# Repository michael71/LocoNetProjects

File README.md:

# LocoNetProjects

Model Railroad Arduino Projects based on LocoNet and MRRWA code (see https://github.com/mrrwa )

Hardware is "OpenHardware" and in some cases is ported from https://opensx.net projects.

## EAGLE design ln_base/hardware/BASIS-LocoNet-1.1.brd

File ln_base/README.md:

# LocoNetProjects - LN-Base-1.0

Based on the design of the opensx-project "Basisplatine" (see https://opensx.net/projekte/basisplatine/rj45/ ), a new board was designed with an LN interface but the same pin layout for add-on boards - to be able to re-use some of the opensx designs

BETA-currently.

(c) Michael Blank 2017

Model Railroad Arduino Projects based on LocoNet and MRRWA code (see https://github.com/mrrwa )

Hardware is "OpenHardware" and in some cases is ported from https://opensx.net projects.

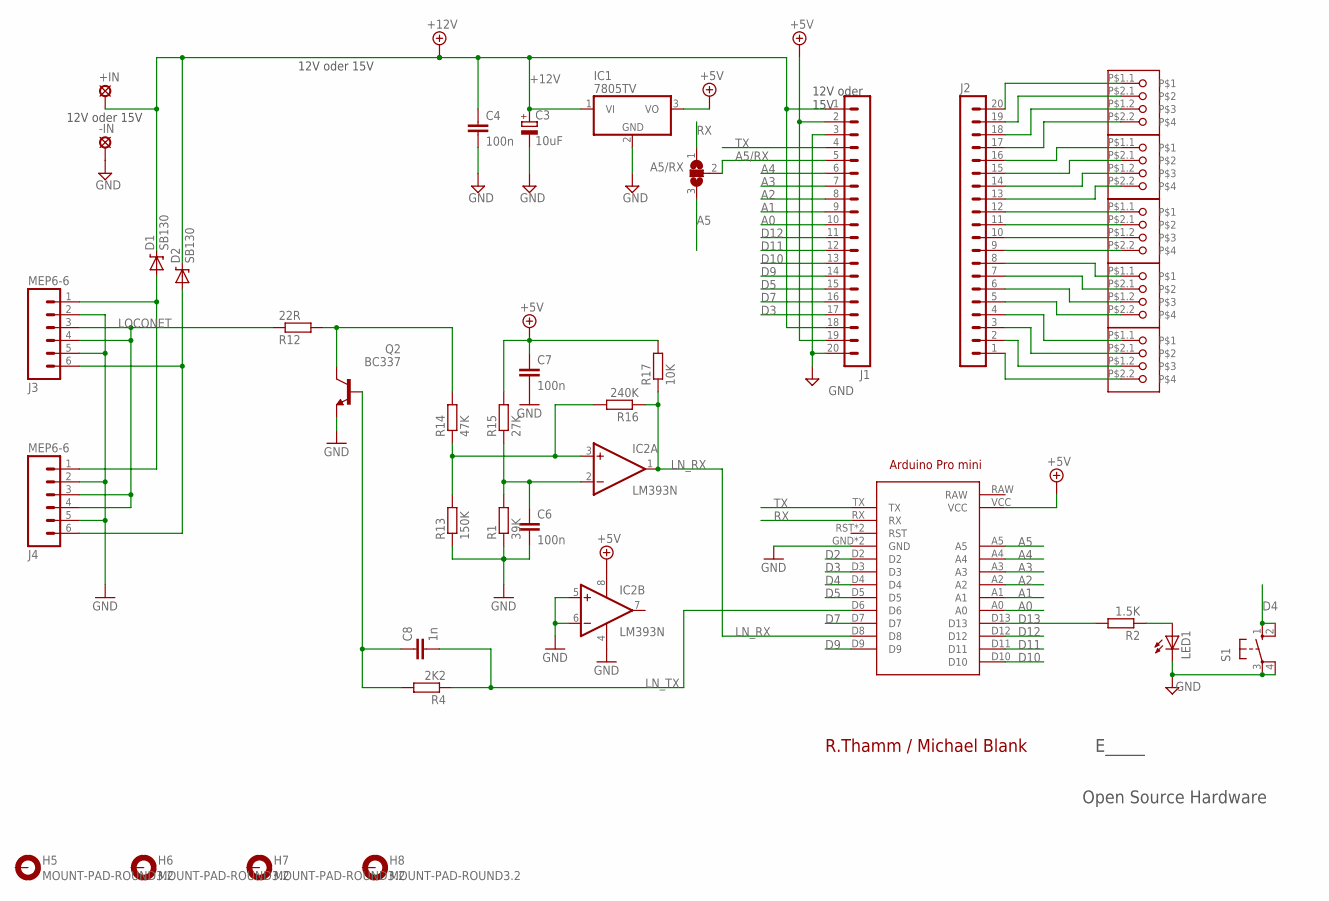
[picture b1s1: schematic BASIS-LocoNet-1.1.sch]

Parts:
+IN: LSP13
-IN: LSP13
A5/RX: SJ2W; SJ_2
ARDUINO2: ArduinoProMini_5V; ARDUINO_PRO_MINI
C3: 10uF; E2,5-7
C4: 100n; C050-025X075
C6, C7: 100n; C025-025X050
C8: 1n; C025-025X050
D1, D2: SB130; DIODE-ZENER
H5, H6, H7, H8: MOUNT-PAD-ROUND3.2; 3,2-PAD
IC1: 7805TV; TO220V
IC2: LM393N; DIL08
J1, J2: MA20-1
J3, J4: MEP6-6; RJ11-6
LED1: LED3MM
Q2: BC337; TO92
R1: 39K; 0207/10
R2: 1.5K; 0207/10
R4: 2K2; 0207/10
R12: 22R; 0207/10
R13: 150K; 0207/10
R14: 47K; 0207/10
R15: 27K; 0207/10
R16: 240K; 0207/10
R17: 10K; 0207/10
S1: 10-XX; B3F-10XX
U$1, U$2, U$3, U$4, U$5: AKL093-06

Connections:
+5V: ARDUINO2.VCC, C7.1, IC1.3 (VO), IC2.8 (V+), J1.2, J1.19, R15.2, R17.2
+12V: +IN.MP, C3.+, C4.1, D1.P$1 (C), D2.P$1 (C), IC1.1 (VI), J1.1, J1.18
A0: ARDUINO2.A0, J1.10
A1: ARDUINO2.A1, J1.9
A2: ARDUINO2.A2, J1.8
A3: ARDUINO2.A3, J1.7
A4: ARDUINO2.A4, J1.6
A5: A5/RX.3, ARDUINO2.A5
A5/RX: A5/RX.2, J1.5
D2: ARDUINO2.D2
D3: ARDUINO2.D3, J1.17
D4: ARDUINO2.D4, S1.1 (S), S1.2 (S1)
D5: ARDUINO2.D5, J1.15
D7: ARDUINO2.D7, J1.16
D9: ARDUINO2.D9, J1.14
D10: ARDUINO2.D10, J1.13
D11: ARDUINO2.D11, J1.12
D12: ARDUINO2.D12, J1.11
D13: ARDUINO2.D13, R2.2
GND: -IN.MP, ARDUINO2.GND, ARDUINO2.GND@1 (GND), C3.-, C4.2, C6.2, C7.2, IC1.2 (GND), IC2.4 (V-), IC2.5 (+IN), IC2.6 (-IN), J1.3, J1.20, J3.2, J3.5, J4.2, J4.5, LED1.K (C), Q2.1 (E), R1.1, R13.1, S1.3, S1.4 (P1)
LN_RX: ARDUINO2.D8, IC2.1 (OUT), R16.1, R17.1
LN_TX: ARDUINO2.D6, C8.2, R4.1
LOCONET: J3.3, J3.4, J4.3, J4.4, R12.1
unnamed: LED1.A, R2.1
unnamed: J2.1, U$4.P$2.2
unnamed: J2.2, U$4.P$1.2
unnamed: J2.3, U$4.P$2.1
unnamed: J2.4, U$4.P$1.1
unnamed: J2.5, U$3.P$2.2
unnamed: J2.6, U$3.P$1.2
unnamed: J2.7, U$3.P$2.1
unnamed: J2.8, U$3.P$1.1
unnamed: J2.9, U$1.P$2.2
unnamed: J2.10, U$1.P$1.2
unnamed: J2.11, U$1.P$2.1
unnamed: J2.12, U$1.P$1.1
unnamed: J2.13, U$2.P$2.2
unnamed: J2.14, U$2.P$1.2
unnamed: J2.15, U$2.P$2.1
unnamed: J2.16, U$2.P$1.1
unnamed: J2.17, U$5.P$2.2
unnamed: J2.18, U$5.P$1.2
unnamed: J2.19, U$5.P$2.1
unnamed: J2.20, U$5.P$1.1
unnamed: D1.P$2 (A), J3.1, J4.1
unnamed: C6.1, IC2.2 (-IN), R1.2, R15.1
unnamed: C8.1, Q2.2 (B), R4.2
unnamed: IC2.3 (+IN), R13.2, R14.1, R16.2
unnamed: Q2.3 (C), R12.2, R14.2
unnamed: D2.P$2 (A), J3.6, J4.6
RX: A5/RX.1, ARDUINO2.RX
TX: ARDUINO2.TX, J1.4

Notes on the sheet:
R.Thamm / Michael Blank
Open Source Hardware
E_____
12V oder 15V
12V oder 15V

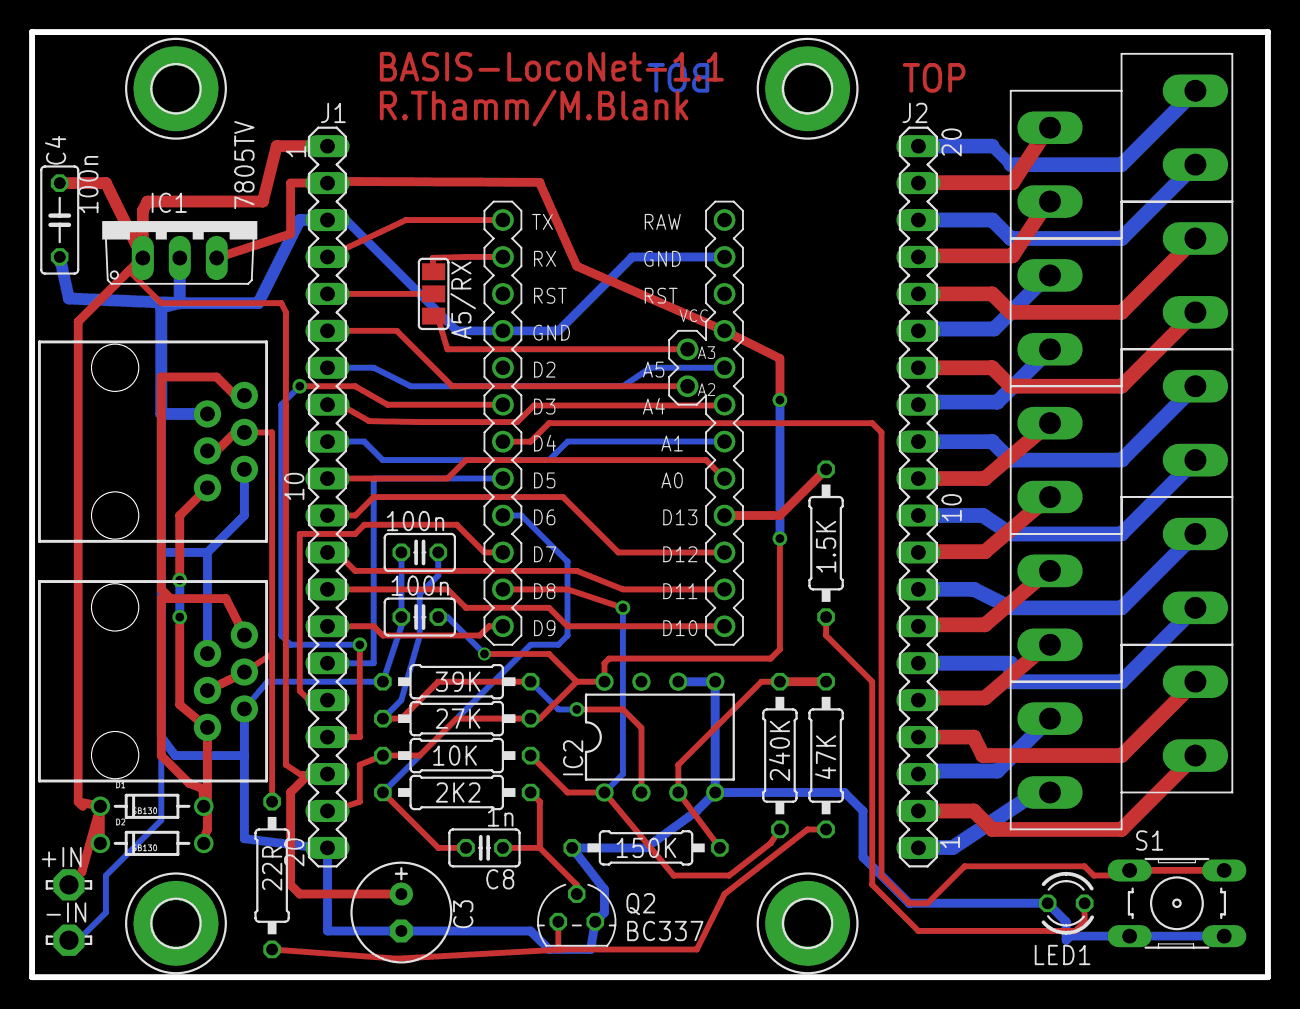
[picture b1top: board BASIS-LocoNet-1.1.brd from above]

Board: 2 copper layers, 85.0 x 65.0 mm, 38 parts (0 on the bottom side), 51 nets.

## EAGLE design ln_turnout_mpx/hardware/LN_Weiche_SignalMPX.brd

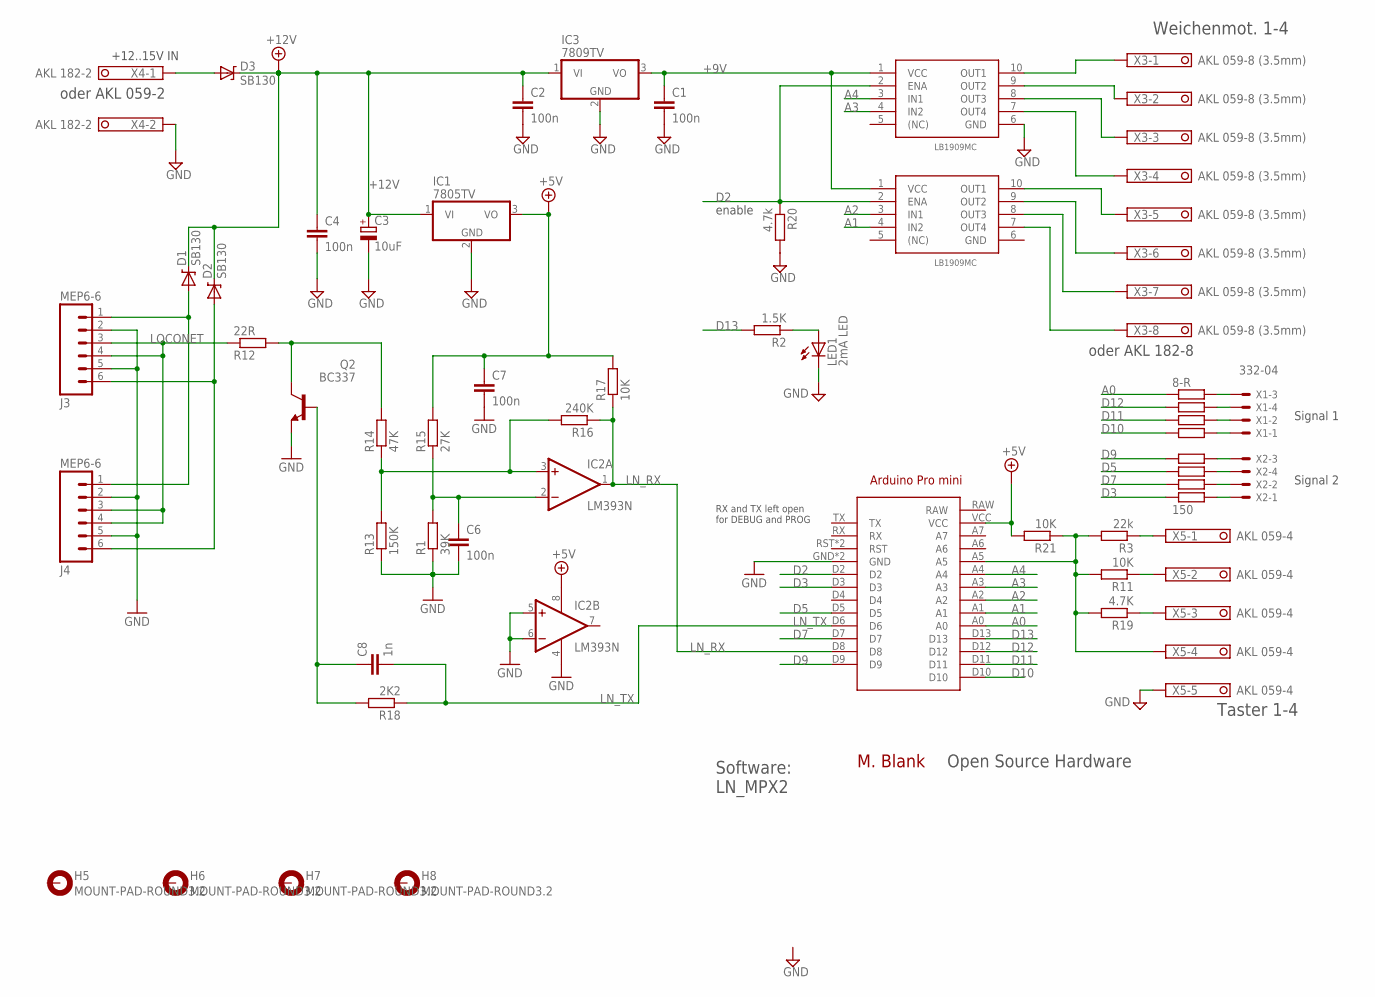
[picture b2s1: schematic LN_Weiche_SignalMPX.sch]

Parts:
8-R: 150; 0207/10
ARDUINO1: ARDUINO_PRO_MINI
C1, C2, C4, C6, C7: 100n; C050-025X075
C3: 10uF; E2,5-7
C8: 1n; C025-025X050
D1, D2, D3: SB130; DIODE-ZENER
H5, H6, H7, H8: MOUNT-PAD-ROUND3.2; 3,2-PAD
IC1: 7805TV; TO220V
IC2: LM393N; DIL08
IC3: 7809TV; TO220V
J3, J4: MEP6-6; RJ11-6
LB1909MC-1, LB1909MC-2: LB1909MC; MSOIC10-1MM
LED1: 2mA LED; LED3MM
Q2: BC337; TO92
R1: 39K; 0207/10
R2: 1.5K; 0207/10
R3: 22k; 0207/10
R4, R5, R6, R7, R8, R9, R10: 150; 0207/10
R11, R17, R21: 10K; 0207/10
R12: 22R; 0207/10
R13: 150K; 0207/10
R14: 47K; 0207/10
R15: 27K; 0207/10
R16: 240K; 0207/10
R18: 2K2; 0207/10
R19: 4.7K; 0207/10
R20: 4.7k; 0207/10
X1, X2: 332-04
X3: AKL 059-8 (3.5mm); 1751303
X4: AKL 182-2; 1751248
X5: AKL 059-4; 1751277

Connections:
+5V: ARDUINO1.VCC, C7.1, IC1.3 (VO), IC2.8 (V+), R15.2, R17.2, R21.2
+9V: C1.1, IC3.3 (VO), LB1909MC-1.1 (VCC), LB1909MC-2.1 (VCC)
+12V: C2.1, C3.+, C4.1, D1.P$1 (C), D2.P$1 (C), D3.P$1 (C), IC1.1 (VI), IC3.1 (VI)
A0: 8-R.1, ARDUINO1.A0
A1: ARDUINO1.A1, LB1909MC-2.4 (IN2)
A2: ARDUINO1.A2, LB1909MC-2.3 (IN1)
A3: ARDUINO1.A3, LB1909MC-1.4 (IN2)
A4: ARDUINO1.A4, LB1909MC-1.3 (IN1)
D2: ARDUINO1.D2, LB1909MC-1.2 (ENA), LB1909MC-2.2 (ENA), R20.1
D3: ARDUINO1.D3, R10.1
D5: ARDUINO1.D5, R8.1
D7: ARDUINO1.D7, R9.1
D9: ARDUINO1.D9, R7.1
D10: ARDUINO1.D10, R6.1
D11: ARDUINO1.D11, R5.1
D12: ARDUINO1.D12, R4.1
D13: ARDUINO1.D13, R2.2
GND: ARDUINO1.GND, ARDUINO1.GND@1 (GND), C1.2, C2.2, C3.-, C4.2, C6.2, C7.2, IC1.2 (GND), IC2.4 (V-), IC2.5 (+IN), IC2.6 (-IN), IC3.2 (GND), J3.2, J3.5, J4.2, J4.5, LB1909MC-1.6 (GND), LB1909MC-2.6 (GND), LED1.K (C), Q2.1 (E), R1.1, R13.1, R20.2, X4.2, X5.5
LN_RX: ARDUINO1.D8, IC2.1 (OUT), R16.1, R17.1
LN_TX: ARDUINO1.D6, C8.2, R18.1
LOCONET: J3.3, J3.4, J4.3, J4.4, R12.1
unnamed: LED1.A, R2.1
unnamed: LB1909MC-1.10 (OUT1), X3.1
unnamed: LB1909MC-1.9 (OUT2), X3.2
unnamed: LB1909MC-1.8 (OUT3), X3.3
unnamed: LB1909MC-1.7 (OUT4), X3.4
unnamed: 8-R.2, X1.3
unnamed: R4.2, X1.4
unnamed: R5.2, X1.2
unnamed: R6.2, X1.1
unnamed: D3.P$2 (A), X4.1
unnamed: R7.2, X2.3
unnamed: R8.2, X2.4
unnamed: R9.2, X2.2
unnamed: R10.2, X2.1
unnamed: LB1909MC-2.10 (OUT1), X3.5
unnamed: LB1909MC-2.9 (OUT2), X3.6
unnamed: LB1909MC-2.8 (OUT3), X3.7
unnamed: LB1909MC-2.7 (OUT4), X3.8
unnamed: ARDUINO1.A5, R3.2, R11.2, R19.2, R21.1, X5.4
unnamed: R3.1, X5.1
unnamed: R11.1, X5.2
unnamed: R19.1, X5.3
unnamed: D1.P$2 (A), J3.1, J4.1
unnamed: C6.1, IC2.2 (-IN), R1.2, R15.1
unnamed: C8.1, Q2.2 (B), R18.2
unnamed: IC2.3 (+IN), R13.2, R14.1, R16.2
unnamed: Q2.3 (C), R12.2, R14.2
unnamed: D2.P$2 (A), J3.6, J4.6

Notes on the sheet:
M. Blank
Open Source Hardware
Signal 1
+12..15V IN
Signal 2
Weichenmot. 1-4
Taster 1-4
oder AKL 059-2
oder AKL 182-8
RX and TX left open for DEBUG and PROG
enable
Software: LN_MPX2

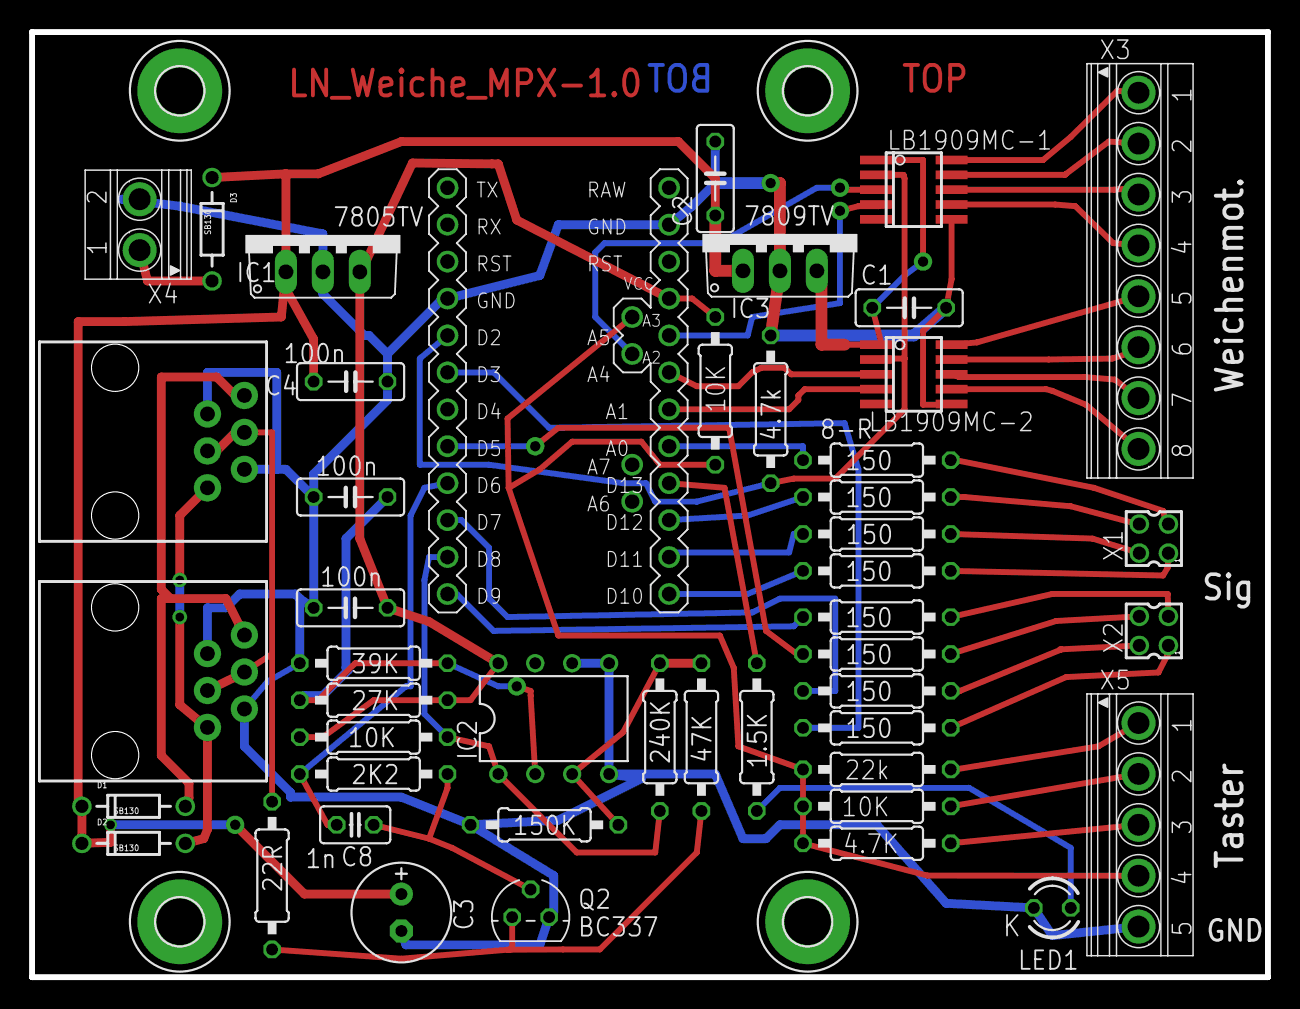
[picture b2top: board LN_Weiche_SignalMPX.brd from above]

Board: 2 copper layers, 85.0 x 65.0 mm, 51 parts (0 on the bottom side), 49 nets.

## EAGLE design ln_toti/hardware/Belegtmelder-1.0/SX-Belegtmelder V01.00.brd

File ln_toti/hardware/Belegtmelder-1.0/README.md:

# Belegtmelder 1.0 Aufsatzplatine

siehe <a href="http://opensx.net/projekte/belegtmelder/"> OpenSX Belegtmelder-Aufsatzplatine</a> - die Dioden 1N5405 werden nur einseitig auf der Platine angelötet, um Platz zu sparen. Die andere Seite ist jeweils an eine in Reihe geschaltete Diode angelötet! 2 dieser "Päarchen" werden antiparallel nebeneinander geschaltet, um den Spannungsabfall auf +/- 1.4 zu begrenzen. Mit dieser Spannung können die Optokoppler LTV844 betrieben werden. Die Arduino Software sorgt dann noch für Filterung und für die Weitergabe an den SX Bus.

Auf der Basisplatine wird NUR EINE REIHE Klemmen verwendet, eine der beiden linken Klemmen dient der Stromzuführung von der SX-Zentrale , an den anderen 8 wird der entsprechende Pol der Gleise angeschlossen. Der zweite Zentralenanschluss wird direkt mit den Gleisen verbunden.

  (siehe auch das größere Foto wegen des Doppeldioden-Aufbaus)

Schaltplan: siehe pdf.

Modul-Gehäuse: Strapubox 524 (das ist die etwas höhere Version) (siehe strapubox.de)

Fotos und HW Design: R. Thamm.

<br />This work is licensed under a <a rel="license" href="http://creativecommons.org/licenses/by-sa/4.0/">Creative Commons Attribution-ShareAlike 4.0 International License</a>.

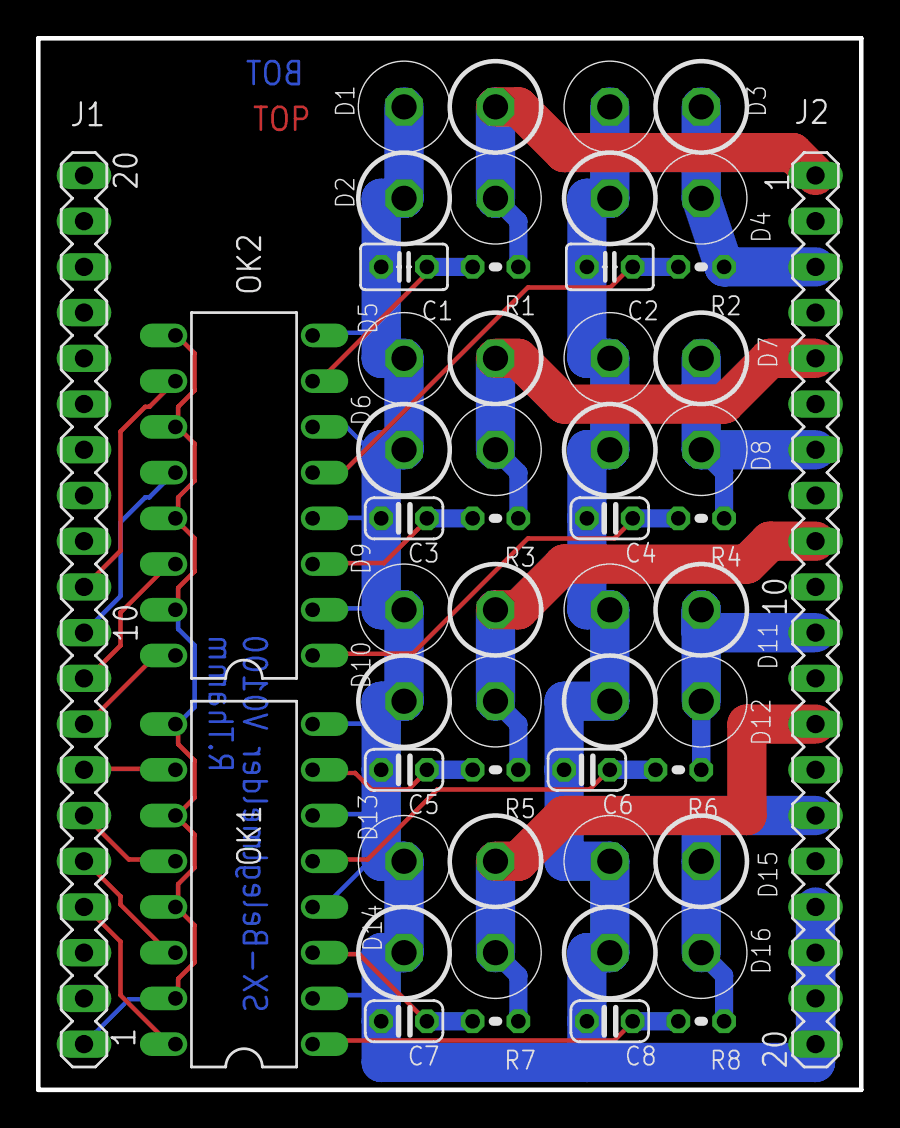
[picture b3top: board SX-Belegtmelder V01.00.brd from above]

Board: 2 copper layers, 45.7 x 58.4 mm, 36 parts (0 on the bottom side), 26 nets.

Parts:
C1, C2: 100n; C025-025X050
C3, C4, C5, C6, C7, C8: 100n; C025-024X044
D1, D2, D3, D4, D5, D6, D7, D8, D9, D10, D11, D12, D13, D14, D15, D16: 2*1N5405; TWIN-DIODE
J1, J2: MA20-1
OK1, OK2: LTV844; DIL16
R1, R2, R3, R4, R5, R6, R7, R8: 33; 0204V

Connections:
unnamed: D1.A, D2.C, J2.1, R1.2
unnamed: D3.A, D4.C, J2.3, R2.2
unnamed: D5.A, D6.C, J2.5, R3.2
unnamed: D7.A, D8.C, J2.7, R4.2
unnamed: D9.A, D10.C, J2.9, R5.2
unnamed: D11.A, D12.C, J2.11, R6.2
unnamed: D13.A, D14.C, J2.13, R7.2
unnamed: D15.A, D16.C, J2.15, R8.2
unnamed: C1.1, C2.1, C3.1, C4.1, C5.1, C6.1, C7.1, C8.1, D1.C, D2.A, D3.C, D4.A, D5.C, D6.A, D7.C, D8.A, D9.C, D10.A, D11.C, D12.A, D13.C, D14.A, D15.C, D16.A, J2.17, J2.18, J2.19, J2.20, OK1.2, OK1.4, OK1.6, OK1.8, OK2.2, OK2.4, OK2.6, OK2.8
unnamed: J1.4, OK1.16
unnamed: J1.5, OK1.14
unnamed: J1.6, OK1.12
unnamed: J1.7, OK1.10
unnamed: J1.8, OK2.16
unnamed: J1.9, OK2.14
unnamed: J1.10, OK2.12
unnamed: C1.2, OK2.7, R1.1
unnamed: C2.2, OK2.5, R2.1
unnamed: C3.2, OK2.3, R3.1
unnamed: C4.2, OK2.1, R4.1
unnamed: C5.2, OK1.7, R5.1
unnamed: C6.2, OK1.5, R6.1
unnamed: C7.2, OK1.3, R7.1
unnamed: C8.2, OK1.1, R8.1
unnamed: J1.11, OK2.10
unnamed: J1.1, OK1.9, OK1.11, OK1.13, OK1.15, OK2.9, OK2.11, OK2.13, OK2.15

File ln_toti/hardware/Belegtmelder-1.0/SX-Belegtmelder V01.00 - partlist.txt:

Partlist

Exported from SX-Belegtmelder V01.00.sch at 26.08.16 14:48

EAGLE Version 7.5.0 Copyright (c) 1988-2015 CadSoft

Assembly variant: 

Part     Value          Device          Package      Library         

C1       100n           C-EU025-025X050 100nF / 2,54mm       
C2       100n           C-EU025-025X050 100nF / 2,54mm          
C3       100n           C-EU025-024X044 100nF / 2,54mm          
C4       100n           C-EU025-024X044 100nF / 2,54mm           
C5       100n           C-EU025-024X044 100nF / 2,54mm         
C6       100n           C-EU025-024X044 100nF / 2,54mm           
C7       100n           C-EU025-024X044 100nF / 2,54mm        
C8       100n           C-EU025-024X044 100nF / 2,54mm        
D1       2*1N5405       TWIN-DIODE      TWIN-DIODE   je 2 Dioden in Reihe geschaltet
D2       2*1N5405       TWIN-DIODE      TWIN-DIODE   ACHTUNG auf Polariät achten
D3       2*1N5405       TWIN-DIODE      TWIN-DIODE   siehe Schaltplan
D4       2*1N5405       TWIN-DIODE      TWIN-DIODE   
D5       2*1N5405       TWIN-DIODE      TWIN-DIODE   
D6       2*1N5405       TWIN-DIODE      TWIN-DIODE   
D7       2*1N5405       TWIN-DIODE      TWIN-DIODE   
D8       2*1N5405       TWIN-DIODE      TWIN-DIODE   
D9       2*1N5405       TWIN-DIODE      TWIN-DIODE   
D10      2*1N5405       TWIN-DIODE      TWIN-DIODE   
D11      2*1N5405       TWIN-DIODE      TWIN-DIODE   
D12      2*1N5405       TWIN-DIODE      TWIN-DIODE   
D13      2*1N5405       TWIN-DIODE      TWIN-DIODE   
D14      2*1N5405       TWIN-DIODE      TWIN-DIODE   
D15      2*1N5405       TWIN-DIODE      TWIN-DIODE   
D16      2*1N5405       TWIN-DIODE      TWIN-DIODE   
J1                      MA20-1          Steckerleiste Raster 2,54mm 20polig, zB Reichelt "MPE 087-1-020
J2                      MA20-1          Steckerleiste Raster 2,54mm 20polig, zB Reichelt "MPE 087-1-020
OK1      LTV844         LTV844          DIL16        optocoupler    
OK2      LTV844         LTV844          DIL16        optocoupler    
R1       33             R-EU_0204/2V    Widerstand 33 Ohm, stehend eingebaut
R2       33             R-EU_0204/2V     
R3       33             R-EU_0204/2V     
R4       33             R-EU_0204/2V    
R5       33             R-EU_0204/2V    
R6       33             R-EU_0204/2V    
R7       33             R-EU_0204/2V    
R8       33             R-EU_0204/2V

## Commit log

2017-09-14 initial version for ln_toti
2017-09-14 added readme files
2017-09-14 initial version of LN-Toti
2017-09-14 add ln->sx bridge readme
2017-09-15 added debug output
2017-09-16 added LNCV programming
2017-09-16 moved LNCV programming to separate file
2017-09-16 ln_toti with LNCV settings. SW Rev 1.10
2017-09-17 LN-Addr of ln_toti now start with XX1, added docu
2017-09-17 corrected docu
2017-09-22 print own ip address(DHCP)
2017-11-11 LocoNetToti corr. startup (EEPROM=65535)
2017-11-11 updated labels.odt
2017-11-12 initial version of LocoNetBidiSXNet.ino
2017-11-12 setting 8 LN-turnouts for a single SX address
2017-11-12 initial version of ln_turnout8
2017-11-16 automatic server ip-addr, bidi working for 4 turnouts
2019-09-25 ln_base 1.1, mpx signal sw
2019-10-02 beginning with ln_turn4_siguk
2019-10-03 initial version of turn4_siguk with 16 LNCVs and 4 turnouts working, no signals
2019-10-04 turn4_siguk - turnouts and signals working, signals without fading
2019-10-05 add feather-inv flag
2019-10-11 added response to SwitchState Request at startup, needs modified LocoNet lib
2019-10-12 leds on/off with fading, reload LNCV after LNCV programming
2019-10-15 new module GP-OUT8, working sw w/o flickering

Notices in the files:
parts and their libraries:
SparkFun-Connectors: Licensing: CC v3.0 Share-Alike You are welcome to use this library for commercial purposes.
